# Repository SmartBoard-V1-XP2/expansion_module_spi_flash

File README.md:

# Expansion Module: SPI Flash

## Overview
The *Expansion Module: SPI Flash* is designed for interfacing with FPGA on the SmartBoard platform. It provides an SPI interface for connecting flash memory, allowing the module to serve both as a data source and a tool for learning and testing SPI flash interfacing. The module utilizes a single socket from the SmartBoard, making it an efficient solution for expanding the board's capabilities.

### Key Features
- SPI interface for easy connection to flash memory.
- Compatible with SmartBoard's single socket interface.
- Ideal for both practical applications and educational purposes in SPI interfacing.

## Design Files

### Schematic Diagram

### Board Layout

## License
The *Expansion Module: SPI Flash* project is released under the MIT License, granting permission to use, modify, and distribute this design in both private and commercial settings.

- **Permission to Use**: You are free to use, modify, and distribute this design in both private and commercial settings.
- **Attribution Requirement**: While not required, attribution to the original author, Adam Łuczak, is appreciated. This can be done through a citation or a link back to this repository.
- **No Warranty**: This design is provided "as is", without warranty of any kind. Use it at your own risk.
- **Liability**: The author is not liable for any damages or losses that may arise from the use of this design.

For the full terms and conditions, please refer to the MIT License documentation.

## Contact
For any inquiries or suggestions about the *Expansion Module: SPI Flash* project, please feel free to contact Adam Łuczak at adam.luczak@outlook.com.

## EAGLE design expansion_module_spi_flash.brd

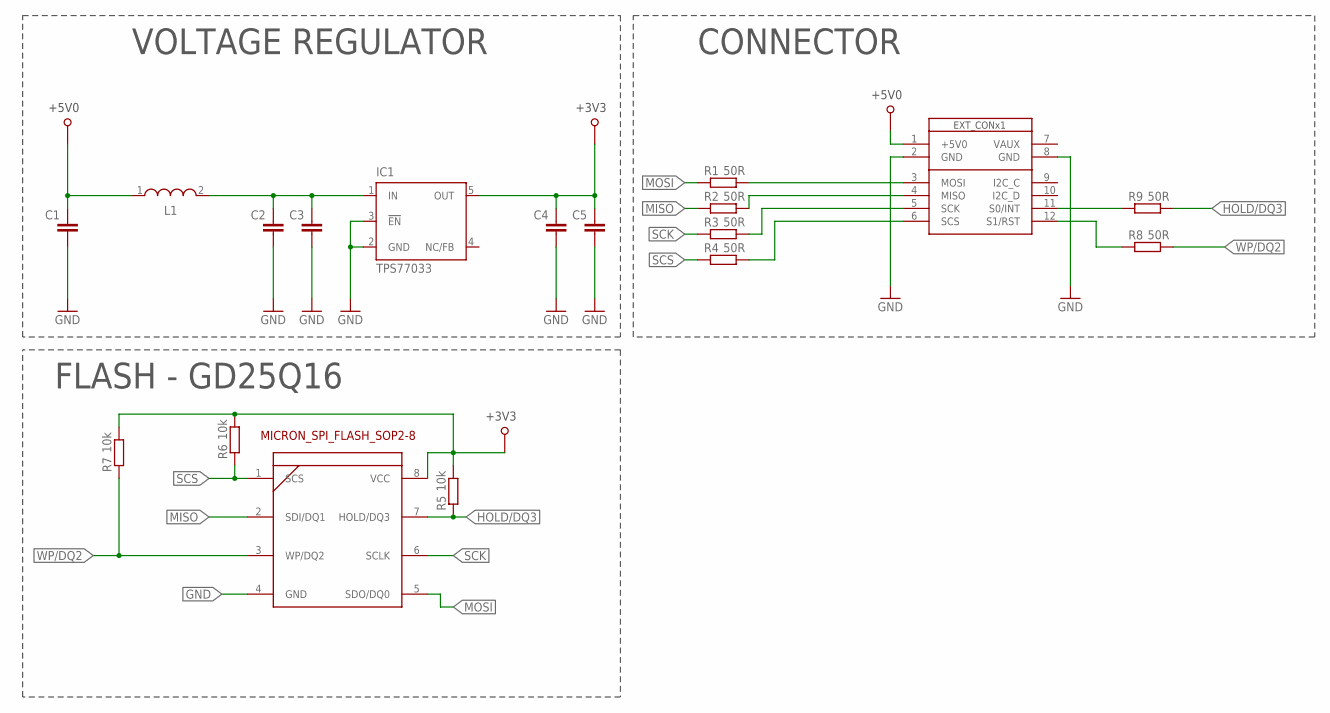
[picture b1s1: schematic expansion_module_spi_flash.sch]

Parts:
C1, C2, C3, C4, C5: C-EUC0805; C0805
IC1: TPS77033; SOT23-DBV
L1: WE-LQ_1210; WE-LQ_M
R1, R2, R3, R4, R8, R9: 50R; R0805
R5, R6, R7: 10k; R0805
U$1: SB_EXT_CON_X1_SPI; SB_EXT_CON_X1_FULL
U$11: MICRON_SPI_FLASH; SO-08M

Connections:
+3V3: C4.2, C5.2, IC1.5 (OUT), R5.2, R6.2, R7.2, U$11.8 (VCC)
+5V0: C1.2, L1.1, U$1.1 (+5V0)
GND: C1.1, C2.1, C3.1, C4.1, C5.1, IC1.2 (GND), IC1.3 (!EN), U$1.2 (GND), U$1.8 (GND), U$11.4 (GND)
HOLD/DQ3: R5.1, R9.2, U$11.7 (HOLD/DQ3)
MISO: R2.1, U$11.2 (SDI/DQ1)
MOSI: R1.1, U$11.5 (SDO/DQ0)
unnamed: R1.2, U$1.3 (MOSI)
unnamed: R2.2, U$1.4 (MISO)
unnamed: R3.2, U$1.5 (SCK)
unnamed: R4.2, U$1.6 (SCS)
unnamed: R8.1, U$1.12 (S1/RST)
unnamed: R9.1, U$1.11 (S0/INT)
unnamed: C2.2, C3.2, IC1.1 (IN), L1.2
SCK: R3.1, U$11.6 (SCLK)
SCS: R4.1, R6.1, U$11.1 (SCS)
WP/DQ2: R7.1, R8.2, U$11.3 (WP/DQ2)

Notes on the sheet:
CONNECTOR
VOLTAGE REGULATOR
FLASH - GD25Q16

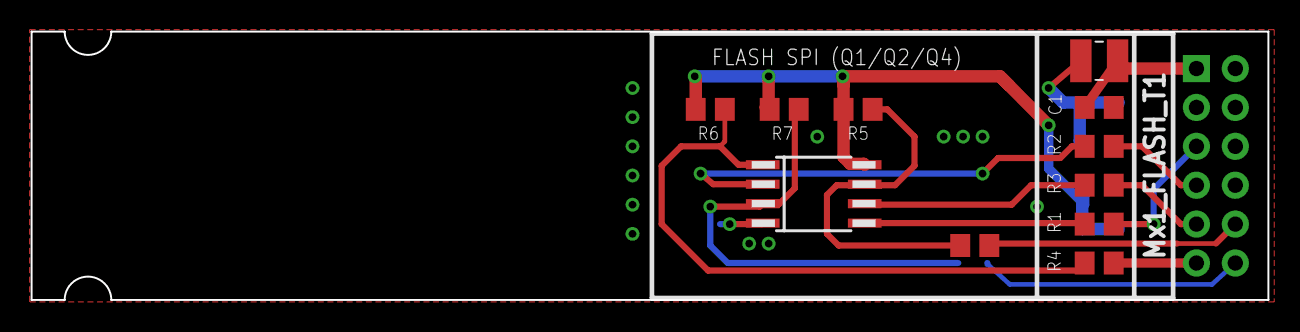
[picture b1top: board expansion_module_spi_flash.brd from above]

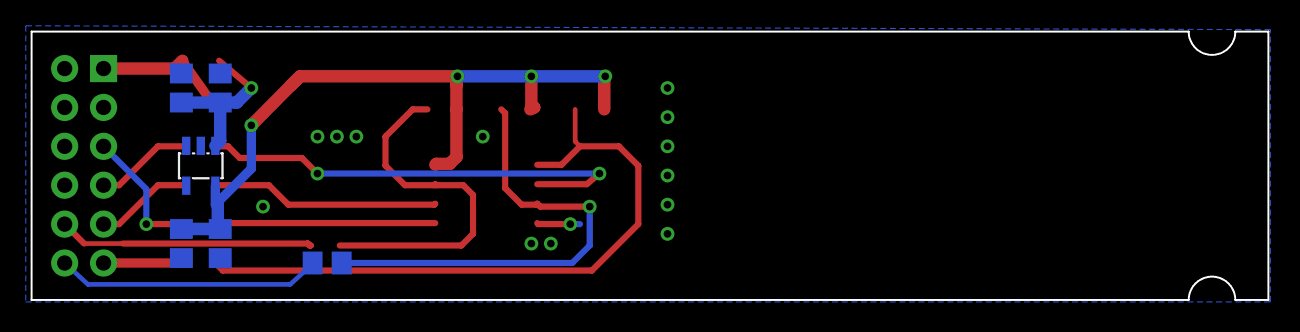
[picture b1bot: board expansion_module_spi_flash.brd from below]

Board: 2 copper layers, 80.8 x 17.5 mm, 18 parts (6 on the bottom side), 16 nets.

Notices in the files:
README.md:
License: MIT
parts and their libraries:
EagleLibrary_Wuerth_Elektronik_eiSos_rev: Copyright: Würth Elektronik
